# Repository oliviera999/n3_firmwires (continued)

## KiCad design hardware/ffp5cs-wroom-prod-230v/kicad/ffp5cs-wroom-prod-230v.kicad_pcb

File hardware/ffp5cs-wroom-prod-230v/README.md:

# Carte porteuse ffp5cs `wroom-prod` — VARIANTE 230 V (KiCad)

Variante **secteur** de la carte porteuse [`hardware/ffp5cs-wroom-prod/`](../ffp5cs-wroom-prod/)
(qui reste la référence 12/24 V). Même firmware, même brochage (vérifié contre
`ffp5cs/include/pins.h`), mais **6 relais** (4 métier + **2 auxiliaires AUX1/AUX2**,
GPIO 23/25, firmware ≥ v15.26) commutent des **charges 230 V ≤ 10 A** dans une
**zone secteur physiquement isolée**, et la connectique est pensée « zéro
soudure » : tout se branche en borniers à vis ou en Dupont.

```
kicad/ffp5cs-wroom-prod-230v.*   Projet KiCad 8 (schéma, PCB ROUTÉ, règles DRC .kicad_dru)
exports/gerbers-*.zip            Fabrication (Gerbers + perçages) — 234 x 110 mm, 2 couches
BOM.csv                          Nomenclature
ACHATS.md                        Liste d'achat complète (BOM + périphériques + boîtier + outillage)
generator/generate.py            Régénère schéma + PCB (non routé) + BOM depuis pinmap.json
generator/route_230v.py          Pipeline de routage sécurisé (voir ci-dessous)
tools/check_pinmap_vs_firmware.py  Garde anti-dérive code <-> plan
```

## Sécurité 230 V — comment c'est construit

- **Zone secteur dédiée** en haut de carte : seuls les contacts relais, leurs pistes
  (2,5 mm) et les borniers y vivent. Les plans de masse et le routage logique en sont
  **exclus par construction** (zones interdites pendant l'autoroutage, pours GND
  arrêtés à la frontière).
- **Fentes d'isolement fraisées** entre les 6 canaux, à la frontière droite de la
  zone, et de part et d'autre du pad COM de chaque relais (le point faible du
  boîtier SRD, où COM passe à ~3,5 mm de la bobine).
- **Règle DRC dédiée** (`.kicad_dru`) : tout cuivre de classe `Mains` doit rester à
  **≥ 3 mm** de tout cuivre non-Mains — vérifiée par `kicad-cli pcb drc` **et** par
  un contrôle géométrique indépendant dans `route_230v.py` (double ceinture).
- Routage secteur **déterministe, tracé en dur** (pas d'autorouteur dans la zone) :
  lignes droites bornier ↔ contacts, COM passant entre les broches bobine.
- Sérigraphie : « ZONE 230V — DANGER », « NC COM NO » sous chaque bornier.
- État validé : **DRC 0 violation, 0 pad non connecté, contrôle 3 mm : 0 écart**
  (KiCad 8.0.9).

### Ce qui reste À TA CHARGE côté installation (non négociable)

1. **Protection amont** : chaque circuit 230 V commuté doit être protégé par
   fusible/disjoncteur + différentiel 30 mA. Il n'y a **pas de fusible sur la carte**
   (choix : la protection appartient au tableau/à la ligne, comme sur les modules
   relais du commerce).
2. **Boîtier obligatoire**, borniers 230 V inaccessibles au doigt, presse-étoupes.
3. Charges inductives (pompe 230 V) : prévoir un **snubber RC ou une varistance côté
   charge** pour préserver les contacts.
4. Relais SRD-05 = isolation bobine/contact d'un relais grand public (type modules
   Arduino). Pour un usage durable/humide, un relais à meilleure séparation
   (ex. Hongfa HF115F) est un upgrade raisonnable — footprint à adapter.
5. Ne jamais intervenir carte sous tension (la sérigraphie te le rappelle).

## Les trois demandes spécifiques de cette variante

- **Zéro soudure à l'usage** : charges sur borniers à vis 5,08 mm ; capteurs sur JST-XH ;
  servos, OLED, I2C sur headers ; DS18B20 et LDR sur borniers ; alim sur jack **ou** bornier.
- **TOUS les GPIO libres accessibles** sur le header J17 (1×12, Dupont) :
  `3V3, GND, EN, RX0, TX0, IO5, IO14, IO17, IO32, IO35, IO36, IO39`
  (IO35/36/39 = entrées seules ; RX0/TX0 à laisser libres pendant un flash USB ;
  IO23/IO25 ne sont plus des spares : ils pilotent les relais AUX1/AUX2).
- **Distribution d'alim supplémentaire** : bornier 5 V/GND (J18), bornier 3V3/GND (J19),
  et rail header 6 points J20 (2×5V, 2×GND, 2×3V3) pour brancher des modules en Dupont.
- **3 ports I2C libres** (J14, J21, J22 — brochage GND/VCC/SCL/SDA) en plus de
  l'OLED : 3-4 modules simultanés avec les pull-ups 4,7 k (bus < ~50 cm).

## Vue Fritzing (câblage de prototype)

`fritzing/ffp5cs-wroom-prod-230v-cablage.fzz` (Fritzing ≥ 1.0, généré par
`generator/generate_fritzing.py`) : câblage breadboard périphériques ↔ DevKit
(capteurs, servos, OLED, pull-ups), plus les headers breakout GPIO (J17, 14 pts)
et rail d'alim (J20). ⚠️ Les charges **230 V n'y figurent pas** : elles se câblent
exclusivement sur les borniers NC/COM/NO de la zone secteur de la carte, jamais
en Dupont. Ouverture vérifiée dans Fritzing (« Routing completed »).

## Régénérer / rerouter / vérifier

```bash
cd hardware/ffp5cs-wroom-prod-230v
python3 generator/generate.py          # schéma + PCB placé (NON routé) + BOM
python3 generator/route_230v.py        # autoroute la logique, trace le secteur en dur,
                                       # coud les masses, corrige les reliefs, contrôle 3 mm
python3 generator/tidy_silkscreen.py   # sérigraphie : repères vs étiquettes
python3 generator/export_fab.py        # zip Gerbers prêt JLCPCB
python3 tools/check_pinmap_vs_firmware.py
kicad-cli pcb drc --severity-error kicad/ffp5cs-wroom-prod-230v.kicad_pcb -o /tmp/drc.rpt
```

⚠️ `generate.py` écrase le PCB routé — enchaîner systématiquement avec `route_230v.py`.
Le routage livré dans `kicad/` est déjà fait et validé.

## Différences avec la carte 12/24 V

| | 12/24 V (`ffp5cs-wroom-prod`) | 230 V (ce dossier) |
|---|---|---|
| Zone secteur isolée + fentes | non (inutile) | **oui** |
| Pistes contacts relais | 2,0 mm | 2,5 mm, tracées à la main |
| Règle DRC 3 mm mains↔logique | — | **oui (.kicad_dru + contrôle python)** |
| Relais | 4 (12/24 V) | **6 (230 V, dont AUX1/AUX2 pilotés serveur)** |
| GPIO libres en header | 10 broches | **12 broches (tout le restant, dont RX0/TX0/36/39)** |
| Distribution 5V/3V3/GND | — | **2 borniers + rail 6 points** |
| Ports I2C libres | 3 (J14/J18/J19) | 3 (J14/J21/J22) |
| Taille | 150×100 mm | 234×110 mm |

Empreintes : bibliothèque officielle KiCad 8.0.9 (CC-BY-SA 4.0 + exception d'usage),
vendorées dans `generator/footprints/`.

Commander la carte : voir **[../COMMANDE_JLCPCB.md](../COMMANDE_JLCPCB.md)**.

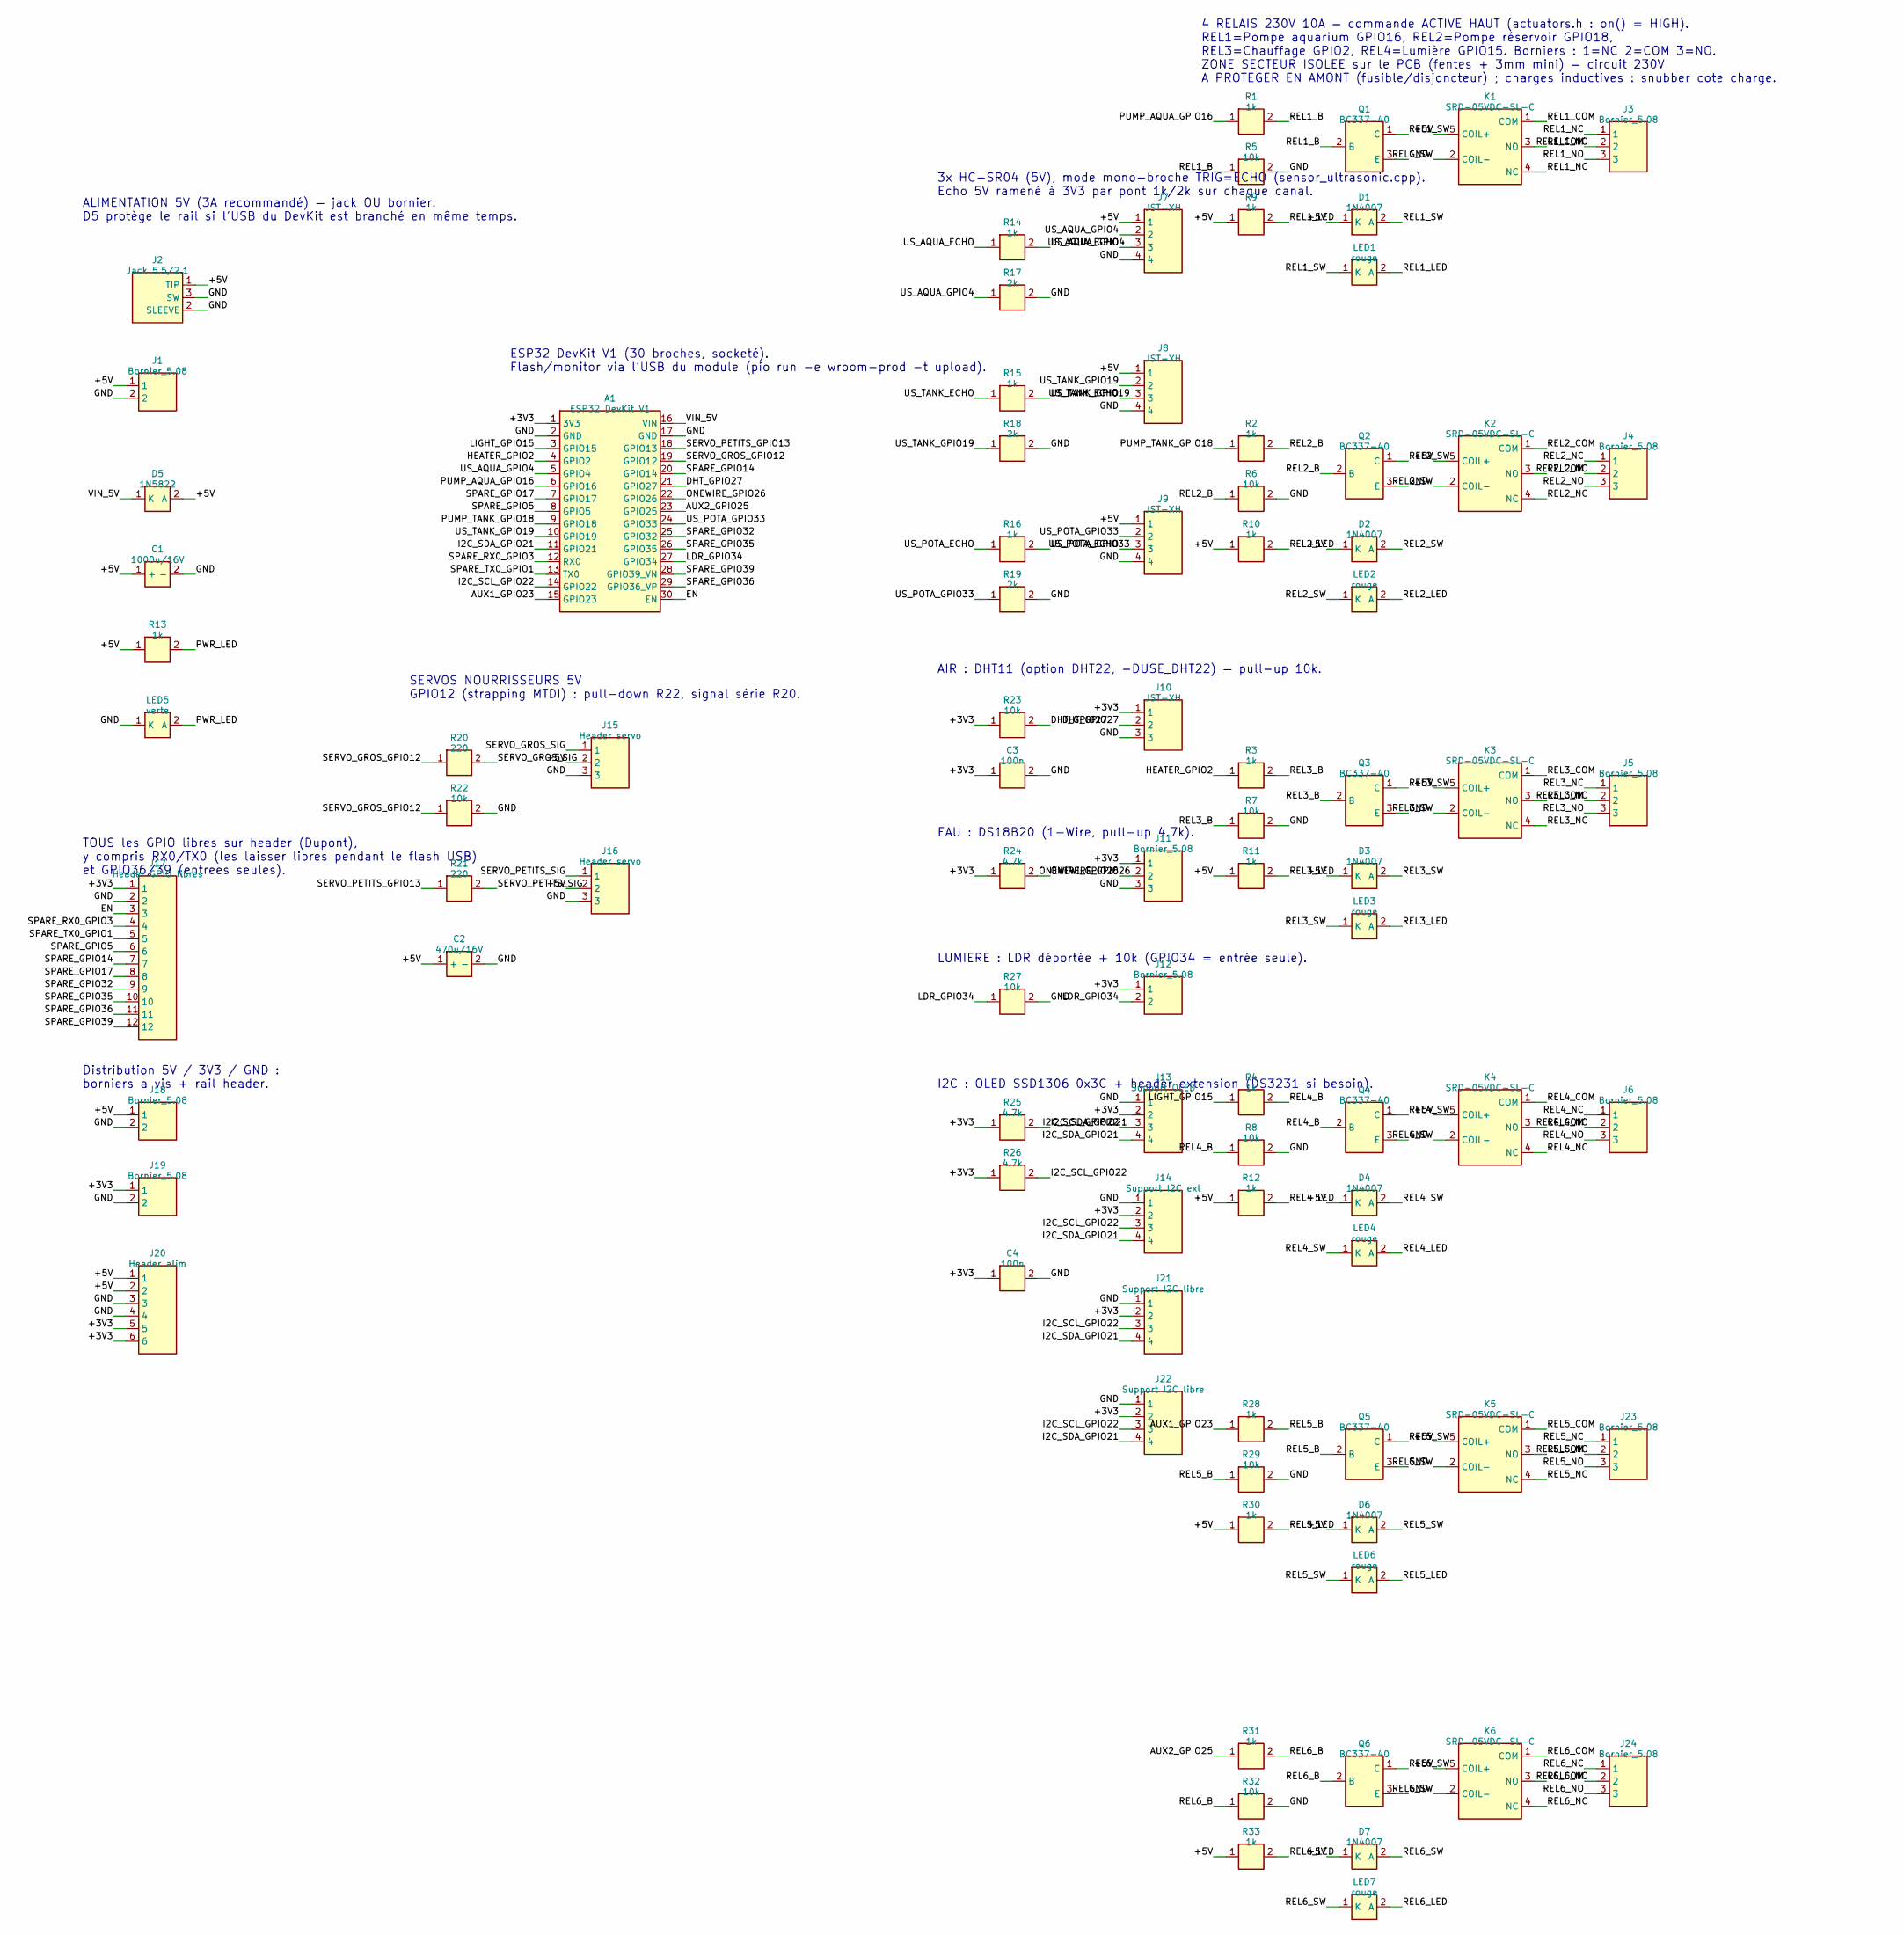
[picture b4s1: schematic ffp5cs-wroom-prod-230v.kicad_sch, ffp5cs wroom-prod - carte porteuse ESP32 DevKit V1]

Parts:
A1: ESP32 DevKit V1; ESP32_DevKit_V1_30pin
C1: 1000u/16V; CP_Radial_D10.0mm_P5.00mm
C2: 470u/16V; CP_Radial_D8.0mm_P3.50mm
C3, C4: 100n; C_Disc_D5.0mm_W2.5mm_P5.00mm
D1, D2, D3, D4, D6, D7: 1N4007; D_DO-41_SOD81_P10.16mm_Horizontal
D5: 1N5822; D_DO-201AD_P15.24mm_Horizontal
J1, J12, J18, J19: Bornier_5.08; TerminalBlock_bornier-2_P5.08mm
J2: Jack 5.5/2.1; BarrelJack_Horizontal
J3, J4, J5, J6, J11, J23, J24: Bornier_5.08; TerminalBlock_bornier-3_P5.08mm
J7, J8, J9: JST-XH; JST_XH_B4B-XH-A_1x04_P2.50mm_Vertical
J10: JST-XH; JST_XH_B3B-XH-A_1x03_P2.50mm_Vertical
J13: Support OLED; PinSocket_1x04_P2.54mm_Vertical
J14: Support I2C ext; PinSocket_1x04_P2.54mm_Vertical
J15, J16: Header servo; PinHeader_1x03_P2.54mm_Vertical
J17: Header GPIO libres; PinHeader_1x12_P2.54mm_Vertical
J20: Header alim; PinHeader_1x06_P2.54mm_Vertical
J21, J22: Support I2C libre; PinSocket_1x04_P2.54mm_Vertical
K1, K2, K3, K4, K5, K6: SRD-05VDC-SL-C; Relay_SPDT_SANYOU_SRD_Series_Form_C
LED1, LED2, LED3, LED4, LED6, LED7: rouge; LED_D5.0mm
LED5: verte; LED_D5.0mm
Q1, Q2, Q3, Q4, Q5, Q6: BC337-40; TO-92_Inline
R1, R2, R3, R4, R9, R10, R11, R12, R13, R14, R15, R16, R28, R30, R31, R33: 1k; R_Axial_DIN0207_L6.3mm_D2.5mm_P10.16mm_Horizontal
R5, R6, R7, R8, R22, R23, R27, R29, R32: 10k; R_Axial_DIN0207_L6.3mm_D2.5mm_P10.16mm_Horizontal
R17, R18, R19: 2k; R_Axial_DIN0207_L6.3mm_D2.5mm_P10.16mm_Horizontal
R20, R21: 220; R_Axial_DIN0207_L6.3mm_D2.5mm_P10.16mm_Horizontal
R24, R25, R26: 4.7k; R_Axial_DIN0207_L6.3mm_D2.5mm_P10.16mm_Horizontal

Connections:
+3V3: A1.1 (3V3), C3.1, C4.1, J10.1, J11.1, J12.1, J13.2, J14.2, J17.1, J19.1, J20.5, J20.6, J21.2, J22.2, R23.1, R24.1, R25.1, R26.1
+5V: C1.1 (+), C2.1 (+), D1.1 (K), D2.1 (K), D3.1 (K), D4.1 (K), D5.2 (A), D6.1 (K), D7.1 (K), J1.1, J2.1 (TIP), J7.1, J8.1, J9.1, J15.2, J16.2, J18.1, J20.1, J20.2, K1.5 (COIL+), K2.5 (COIL+), K3.5 (COIL+), K4.5 (COIL+), K5.5 (COIL+), K6.5 (COIL+), R9.1, R10.1, R11.1, R12.1, R13.1, R30.1, R33.1
AUX1_GPIO23: A1.15 (GPIO23), R28.1
AUX2_GPIO25: A1.23 (GPIO25), R31.1
DHT_GPIO27: A1.21 (GPIO27), J10.2, R23.2
EN: A1.30 (EN), J17.3
GND: A1.2 (GND), A1.17 (GND), C1.2 (-), C2.2 (-), C3.2, C4.2, J1.2, J2.2 (SLEEVE), J2.3 (SW), J7.4, J8.4, J9.4, J10.3, J11.3, J13.1, J14.1, J15.3, J16.3, J17.2, J18.2, J19.2, J20.3, J20.4, J21.1, J22.1, LED5.1 (K), Q1.3 (E), Q2.3 (E), Q3.3 (E), Q4.3 (E), Q5.3 (E), Q6.3 (E), R5.2, R6.2, R7.2, R8.2, R17.2, R18.2, R19.2, R22.2, R27.2, R29.2, R32.2
HEATER_GPIO2: A1.4 (GPIO2), R3.1
I2C_SCL_GPIO22: A1.14 (GPIO22), J13.3, J14.3, J21.3, J22.3, R26.2
I2C_SDA_GPIO21: A1.11 (GPIO21), J13.4, J14.4, J21.4, J22.4, R25.2
LDR_GPIO34: A1.27 (GPIO34), J12.2, R27.1
LIGHT_GPIO15: A1.3 (GPIO15), R4.1
ONEWIRE_GPIO26: A1.22 (GPIO26), J11.2, R24.2
PUMP_AQUA_GPIO16: A1.6 (GPIO16), R1.1
PUMP_TANK_GPIO18: A1.9 (GPIO18), R2.1
PWR_LED: LED5.2 (A), R13.2
REL1_B: Q1.2 (B), R1.2, R5.1
REL1_COM: J3.2, K1.1 (COM)
REL1_LED: LED1.2 (A), R9.2
REL1_NC: J3.1, K1.4 (NC)
REL1_NO: J3.3, K1.3 (NO)
REL1_SW: D1.2 (A), K1.2 (COIL-), LED1.1 (K), Q1.1 (C)
REL2_B: Q2.2 (B), R2.2, R6.1
REL2_COM: J4.2, K2.1 (COM)
REL2_LED: LED2.2 (A), R10.2
REL2_NC: J4.1, K2.4 (NC)
REL2_NO: J4.3, K2.3 (NO)
REL2_SW: D2.2 (A), K2.2 (COIL-), LED2.1 (K), Q2.1 (C)
REL3_B: Q3.2 (B), R3.2, R7.1
REL3_COM: J5.2, K3.1 (COM)
REL3_LED: LED3.2 (A), R11.2
REL3_NC: J5.1, K3.4 (NC)
REL3_NO: J5.3, K3.3 (NO)
REL3_SW: D3.2 (A), K3.2 (COIL-), LED3.1 (K), Q3.1 (C)
REL4_B: Q4.2 (B), R4.2, R8.1
REL4_COM: J6.2, K4.1 (COM)
REL4_LED: LED4.2 (A), R12.2
REL4_NC: J6.1, K4.4 (NC)
REL4_NO: J6.3, K4.3 (NO)
REL4_SW: D4.2 (A), K4.2 (COIL-), LED4.1 (K), Q4.1 (C)
REL5_B: Q5.2 (B), R28.2, R29.1
REL5_COM: J23.2, K5.1 (COM)
REL5_LED: LED6.2 (A), R30.2
REL5_NC: J23.1, K5.4 (NC)
REL5_NO: J23.3, K5.3 (NO)
REL5_SW: D6.2 (A), K5.2 (COIL-), LED6.1 (K), Q5.1 (C)
REL6_B: Q6.2 (B), R31.2, R32.1
REL6_COM: J24.2, K6.1 (COM)
REL6_LED: LED7.2 (A), R33.2
REL6_NC: J24.1, K6.4 (NC)
REL6_NO: J24.3, K6.3 (NO)
REL6_SW: D7.2 (A), K6.2 (COIL-), LED7.1 (K), Q6.1 (C)
SERVO_GROS_GPIO12: A1.19 (GPIO12), R20.1, R22.1
SERVO_GROS_SIG: J15.1, R20.2
SERVO_PETITS_GPIO13: A1.18 (GPIO13), R21.1
SERVO_PETITS_SIG: J16.1, R21.2
SPARE_GPIO5: A1.8 (GPIO5), J17.6
SPARE_GPIO14: A1.20 (GPIO14), J17.7
SPARE_GPIO17: A1.7 (GPIO17), J17.8
SPARE_GPIO32: A1.25 (GPIO32), J17.9
SPARE_GPIO35: A1.26 (GPIO35), J17.10
SPARE_GPIO36: A1.29 (GPIO36_VP), J17.11
SPARE_GPIO39: A1.28 (GPIO39_VN), J17.12
SPARE_RX0_GPIO3: A1.12 (RX0), J17.4
SPARE_TX0_GPIO1: A1.13 (TX0), J17.5
US_AQUA_ECHO: J7.3, R14.1
US_AQUA_GPIO4: A1.5 (GPIO4), J7.2, R14.2, R17.1
US_POTA_ECHO: J9.3, R16.1
US_POTA_GPIO33: A1.24 (GPIO33), J9.2, R16.2, R19.1
US_TANK_ECHO: J8.3, R15.1
US_TANK_GPIO19: A1.10 (GPIO19), J8.2, R15.2, R18.1
VIN_5V: A1.16 (VIN), D5.1 (K)

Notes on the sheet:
ALIMENTATION 5V (3A recommandé) — jack OU bornier. D5 protège le rail si l'USB du DevKit est branché en même temps.
ESP32 DevKit V1 (30 broches, socketé). Flash/monitor via l'USB du module (pio run -e wroom-prod -t upload).
SERVOS NOURRISSEURS 5V GPIO12 (strapping MTDI) : pull-down R22, signal série R20.
3x HC-SR04 (5V), mode mono-broche TRIG=ECHO (sensor_ultrasonic.cpp). Echo 5V ramené à 3V3 par pont 1k/2k sur chaque canal.
AIR : DHT11 (option DHT22, -DUSE_DHT22) — pull-up 10k.
EAU : DS18B20 (1-Wire, pull-up 4.7k).
LUMIERE : LDR déportée + 10k (GPIO34 = entrée seule).
I2C : OLED SSD1306 0x3C + header extension (DS3231 si besoin).
4 RELAIS 230V 10A — commande ACTIVE HAUT (actuators.h : on() = HIGH). REL1=Pompe aquarium GPIO16, REL2=Pompe réservoir GPIO18, REL3=Chauffage GPIO2, REL4=Lumière GPIO15. Borniers : 1=NC 2=COM 3=NO. ZONE SECTEUR ISOLEE sur le PCB (fentes + 3mm mini) — circuit 230V A PROTEGER EN AMONT (fusible/disjon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
TOUS les GPIO libres sur header (Dupont), y compris RX0/TX0 (les laisser libres pendant le flash USB) et GPIO36/39 (entrees seules).
Distribution 5V / 3V3 / GND : borniers a vis + rail header.

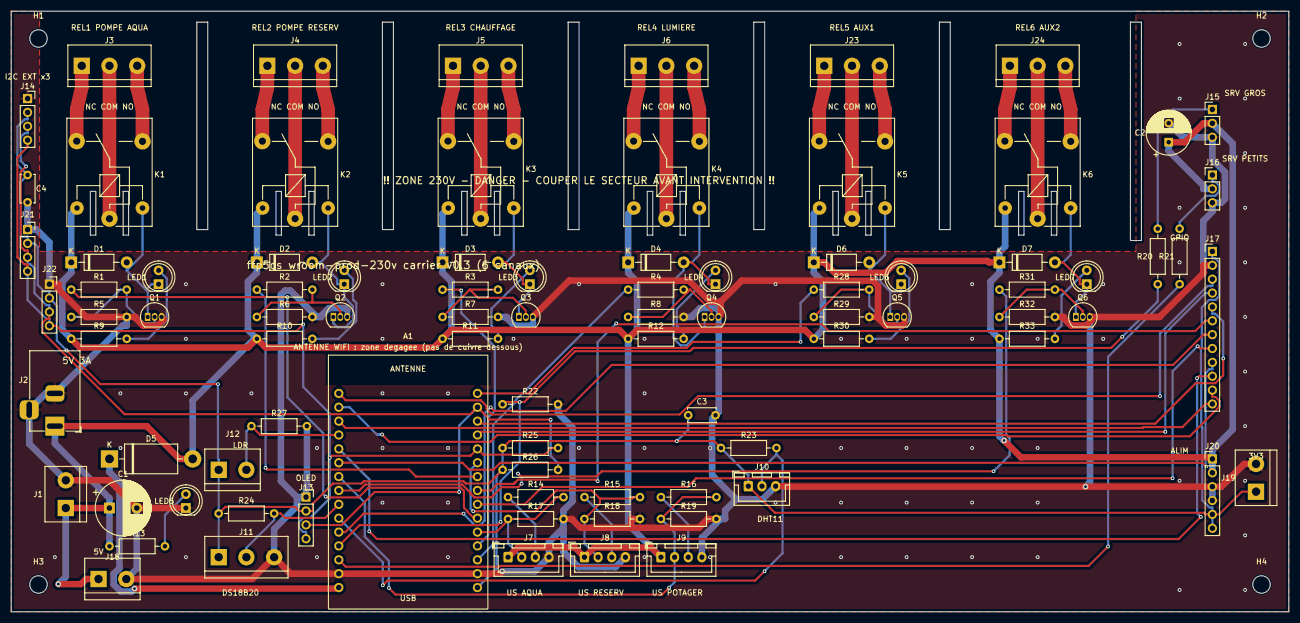
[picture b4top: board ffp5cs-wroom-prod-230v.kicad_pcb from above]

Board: 2 copper layers, 234.0 x 110.0 mm, 92 parts (0 on the bottom side), 72 nets.

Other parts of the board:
H1, H2, H3, H4: M3; MountingHole_3.2mm_M3

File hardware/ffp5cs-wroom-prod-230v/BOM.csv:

Refs;Qte;Valeur;Empreinte;Description
A1;1;ESP32 DevKit V1;ESP32_DevKit_V1_30pin;Module ESP32-WROOM-32 DevKit V1 30 broches, sur 2 supports 1x15
C1;1;1000u/16V;CP_Radial_D10.0mm_P5.00mm;Réservoir rail 5V (relais + servos + HC-SR04)
C2;1;470u/16V;CP_Radial_D8.0mm_P3.50mm;Découplage rail 5V servos
C3;1;100n;C_Disc_D5.0mm_W2.5mm_P5.00mm;Découplage 3V3 capteurs
C4;1;100n;C_Disc_D5.0mm_W2.5mm_P5.00mm;Découplage 3V3 I2C
D1 D2 D3 D4 D6 D7;6;1N4007;D_DO-41_SOD81_P10.16mm_Horizontal;Diode de roue libre bobine
D5;1;1N5822;D_DO-201AD_P15.24mm_Horizontal;Schottky 3A vers VIN DevKit (anti-retour si USB branché)
H1 H2 H3 H4;4;M3;MountingHole_3.2mm_M3;Trou de fixation M3
J1;1;Bornier_5.08;TerminalBlock_bornier-2_P5.08mm;Entrée 5V alternative (bornier, 1=+5V 2=GND)
J10;1;JST-XH;JST_XH_B3B-XH-A_1x03_P2.50mm_Vertical;DHT11/DHT22 (1=3V3 2=DATA 3=GND)
J11;1;Bornier_5.08;TerminalBlock_bornier-3_P5.08mm;Sonde DS18B20 étanche (1=3V3 2=DATA 3=GND)
J12;1;Bornier_5.08;TerminalBlock_bornier-2_P5.08mm;LDR déportée entre 3V3 et l'ADC (1=3V3 2=ADC)
J13;1;Support OLED;PinSocket_1x04_P2.54mm_Vertical;OLED SSD1306 128x64 I2C 0x3C (1=GND 2=VCC 3=SCL 4=SDA)
J14;1;Support I2C ext;PinSocket_1x04_P2.54mm_Vertical;Extension I2C — ex. module DS3231 (1=GND 2=VCC 3=SCL 4=SDA)
J15;1;Header servo;PinHeader_1x03_P2.54mm_Vertical;Servo GROS (1=SIG 2=+5V 3=GND)
J16;1;Header servo;PinHeader_1x03_P2.54mm_Vertical;Servo PETITS (1=SIG 2=+5V 3=GND)
J17;1;Header GPIO libres;PinHeader_1x12_P2.54mm_Vertical;TOUS les GPIO libres (1=3V3 2=GND 3=EN 4=RX0 5=TX0 6=IO5 7=IO14 8=IO17 9=IO32 10=IO35 11=IO36 12=IO39) — IO23/IO25 = relais AUX
J18;1;Bornier_5.08;TerminalBlock_bornier-2_P5.08mm;Distribution 5V (1=+5V 2=GND)
J19;1;Bornier_5.08;TerminalBlock_bornier-2_P5.08mm;Distribution 3V3 (1=+3V3 2=GND)
J2;1;Jack 5.5/2.1;BarrelJack_Horizontal;Entrée 5V 3A (jack, centre = +)
J20;1;Header alim;PinHeader_1x06_P2.54mm_Vertical;Rail Dupont (1-2=+5V 3-4=GND 5-6=+3V3)
J21;1;Support I2C libre;PinSocket_1x04_P2.54mm_Vertical;Port I2C libre 2 (1=GND 2=VCC 3=SCL 4=SDA)
J22;1;Support I2C libre;PinSocket_1x04_P2.54mm_Vertical;Port I2C libre 3 (1=GND 2=VCC 3=SCL 4=SDA)
J23 J24 J3 J4 J5 J6;6;Bornier_5.08;TerminalBlock_bornier-3_P5.08mm;Bornier charge 230V (1=NC 2=COM 3=NO)
J7;1;JST-XH;JST_XH_B4B-XH-A_1x04_P2.50mm_Vertical;HC-SR04 AQUA (1=5V 2=TRIG 3=ECHO 4=GND)
J8;1;JST-XH;JST_XH_B4B-XH-A_1x04_P2.50mm_Vertical;HC-SR04 TANK (1=5V 2=TRIG 3=ECHO 4=GND)
J9;1;JST-XH;JST_XH_B4B-XH-A_1x04_P2.50mm_Vertical;HC-SR04 POTA (1=5V 2=TRIG 3=ECHO 4=GND)
K1 K2 K3 K4 K5 K6;6;SRD-05VDC-SL-C;Relay_SPDT_SANYOU_SRD_Series_Form_C;Relais 5V SPDT 10A/250VAC (Songle/Sanyou SRD)
LED1 LED2 LED3 LED4 LED6 LED7;6;rouge;LED_D5.0mm;LED témoin relais ON
LED5;1;verte;LED_D5.0mm;LED présence 5V
Q1 Q2 Q3 Q4 Q5 Q6;6;BC337-40;TO-92_Inline;Transistor NPN commande relais (1=C 2=B 3=E)
R1 R2 R28 R3 R31 R4;6;1k;R_Axial_DIN0207_L6.3mm_D2.5mm_P10.16mm_Horizontal;Résistance base transistor
R13;1;1k;R_Axial_DIN0207_L6.3mm_D2.5mm_P10.16mm_Horizontal;Résistance LED présence 5V
R14;1;1k;R_Axial_DIN0207_L6.3mm_D2.5mm_P10.16mm_Horizontal;Série écho HC-SR04 AQUA
R15;1;1k;R_Axial_DIN0207_L6.3mm_D2.5mm_P10.16mm_Horizontal;Série écho HC-SR04 TANK
R16;1;1k;R_Axial_DIN0207_L6.3mm_D2.5mm_P10.16mm_Horizontal;Série écho HC-SR04 POTA
R17;1;2k;R_Axial_DIN0207_L6.3mm_D2.5mm_P10.16mm_Horizontal;Pont diviseur écho AQUA (5V->3V3)
R18;1;2k;R_Axial_DIN0207_L6.3mm_D2.5mm_P10.16mm_Horizontal;Pont diviseur écho TANK (5V->3V3)
R19;1;2k;R_Axial_DIN0207_L6.3mm_D2.5mm_P10.16mm_Horizontal;Pont diviseur écho POTA (5V->3V3)
R20;1;220;R_Axial_DIN0207_L6.3mm_D2.5mm_P10.16mm_Horizontal;Série signal servo gros
R21;1;220;R_Axial_DIN0207_L6.3mm_D2.5mm_P10.16mm_Horizontal;Série signal servo petits
R22;1;10k;R_Axial_DIN0207_L6.3mm_D2.5mm_P10.16mm_Horizontal;Pull-down GPIO12 (strapping MTDI : doit être bas au boot)
R23;1;10k;R_Axial_DIN0207_L6.3mm_D2.5mm_P10.16mm_Horizontal;Pull-up data DHT11
R24;1;4.7k;R_Axial_DIN0207_L6.3mm_D2.5mm_P10.16mm_Horizontal;Pull-up bus 1-Wire DS18B20
R25;1;4.7k;R_Axial_DIN0207_L6.3mm_D2.5mm_P10.16mm_Horizontal;Pull-up I2C SDA
R26;1;4.7k;R_Axial_DIN0207_L6.3mm_D2.5mm_P10.16mm_Horizontal;Pull-up I2C SCL
R27;1;10k;R_Axial_DIN0207_L6.3mm_D2.5mm_P10.16mm_Horizontal;Bas du pont diviseur LDR (GPIO34 = entrée seule ADC)
R29 R32 R5 R6 R7 R8;6;10k;R_Axial_DIN0207_L6.3mm_D2.5mm_P10.16mm_Horizontal;Pull-down base (état sûr au boot)
R10 R11 R12 R30 R33 R9;6;1k;R_Axial_DIN0207_L6.3mm_D2.5mm_P10.16mm_Horizontal;Résistance LED témoin
A1 (supports);2;Support femelle 1x15 P2.54;monte sur l'empreinte ESP32_DevKit_V1_30pin;Barrettes femelles 15 pts : le DevKit s'enfiche, jamais soudé

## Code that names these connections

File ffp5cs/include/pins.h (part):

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constexpr int ONE_WIRE_BUS = 41;  // Bus DS18B20 (37 = conflit PSRAM octale)

// I2C (Wire)
constexpr int I2C_SDA = 8;
constexpr int I2C_SCL = 9;

// OLED Display (I2C)
constexpr int OLED_SDA = I2C_SDA;
constexpr int OLED_SCL = I2C_SCL;
constexpr int OLED_ADDR = 0x3C;

// RTC DS3231 (I2C) - optionnel, pour heure précise offline
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
// SD carte (SPI) - optionnel ; broches NON câblées sur la carte porteuse
// (conservées pour compiler le support SD, à câbler via J20 le cas échéant)
constexpr int SD_CS_PIN   = 10;
constexpr int SD_MOSI_PIN = 11;
constexpr int SD_CLK_PIN  = 12;
constexpr int SD_MISO_PIN = 14;

} // namespace Pins

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// Source de vérité : pinmap_universel_propose.json. SD native (10/12/13/14),
// K5/K6 (=AUX1/AUX2) embarqués : GPIO 48 (LED RGB v1.0 : recopie d'état K5,
// cosmétique) et 45 (strapping VDD_SPI : commande via base 1k + pull-down 10k,
// sûre au boot, comme GPIO2/15 sur les cartes historiques).
namespace Pins {
constexpr int ULTRASON_AQUA = 39;  // net US1
constexpr int ULTRASON_TANK = 40;  // net US2
constexpr int ULTRASON_POTA = 41;  // net US3

constexpr int EAU_POTAGER = ULTRASON_POTA; // Alias pour rétrocompatibilité
constexpr int LUMINOSITE = 6;      // net ADC_E (ADC1_CH5)

constexpr int POMPE_AQUA   = 15;   // net K1
constexpr int POMPE_RESERV = 16;   // net K2
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constexpr int AUX1 = 48;           // net AUX1 (K5)
constexpr int AUX2 = 45;           // net AUX2 (K6)

constexpr int SERVO_GROS   = 21;   // net SERVO1
constexpr int SERVO_PETITS = 47;   // net SERVO2

constexpr int DHT_PIN      = 38;   // net DHT_INT (LED RGB v1.1 : scintillement cosmétique)
constexpr int ONE_WIRE_BUS = 42;   // net ONEWIRE

constexpr int I2C_SDA = 8;
constexpr int I2C_SCL = 9;
constexpr int OLED_SDA = I2C_SDA;
constexpr int OLED_SCL = I2C_SCL;
constexpr int OLED_ADDR = 0x3C;
constexpr uint8_t DS3231_I2C_ADDR = 0x68;

// microSD embarquée (slot bi-site de la carte, côté A2)
constexpr int SD_CS_PIN   = 10;
constexpr int SD_MOSI_PIN = 12;
constexpr int SD_CLK_PIN  = 13;
constexpr int SD_MISO_PIN = 14;

} // namespace Pins

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namespace Pins {
constexpr int ULTRASON_AQUA = 4;   // net US1 (partagé PLUIE msp)
constexpr int ULTRASON_TANK = 5;   // net US2 (partagé DHT_EXT msp)
constexpr int ULTRASON_POTA = 14;  // net US3 (= SD_CS en env wroom-sd)

constexpr int EAU_POTAGER = ULTRASON_POTA;
constexpr int LUMINOSITE = 36;     // net ADC_E (entrée seule, ADC1)

constexpr int POMPE_AQUA   = 16;   // net K1 (partagé POMPE n3pp)
constexpr int POMPE_RESERV = 17;   // net K2
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constexpr int AUX1 = 23;           // net AUX1 (K5)
constexpr int AUX2 = 25;           // net AUX2 (K6)

constexpr int SERVO_GROS   = 26;   // net SERVO1 (partagé SERVOGD msp)
constexpr int SERVO_PETITS = 27;   // net SERVO2 (partagé SERVOHB msp)

constexpr int DHT_PIN      = 15;   // net DHT_INT (commun aux 3 firmwares)
constexpr int ONE_WIRE_BUS = 2;    // net ONEWIRE (partagé TempEau msp)

constexpr int I2C_SDA = 21;
constexpr int I2C_SCL = 22;
constexpr int OLED_SDA = I2C_SDA;
constexpr int OLED_SCL = I2C_SCL;
constexpr int OLED_ADDR = 0x3C;
constexpr uint8_t DS3231_I2C_ADDR = 0x68;

// microSD (option env wroom-sd uniquement — lignes sur US3/AUX1/AUX2 + 12)
constexpr int SD_CS_PIN   = 14;
constexpr int SD_CLK_PIN  = 23;
constexpr int SD_MOSI_PIN = 25;
constexpr int SD_MISO_PIN = 12;    // strapping MTDI : ligne SANS pull-up sur la carte

} // namespace Pins

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constexpr int ONE_WIRE_BUS = 37;  // Bus DS18B20

// I2C (Wire) - Pins par défaut pour ESP32-S3 devkit. Vérifier câblage (VCC/GND/SDA/SCL) et pull-ups si OLED erratique (voir i2c_bus.cpp).
constexpr int I2C_SDA = 8;  // GPIO 8 (SDA)
constexpr int I2C_SCL = 9;  // GPIO 9 (SCL)

// OLED Display (I2C)
constexpr int OLED_SDA = I2C_SDA;
constexpr int OLED_SCL = I2C_SCL;
constexpr int OLED_ADDR = 0x3C;  // Adresse I2C de l'OLED

// RTC DS3231 (I2C) - optionnel, pour heure précise offline
constexpr uint8_t DS3231_I2C_ADDR = 0x68;

// SD carte (SPI) - optionnel, broches 10/11/12/14 (libres, non utilisées par les servos)
constexpr int SD_CS_PIN   = 10;
constexpr int SD_MOSI_PIN = 11;
constexpr int SD_CLK_PIN  = 12;
constexpr int SD_MISO_PIN = 14;

} // namespace Pins

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constexpr int ONE_WIRE_BUS = 26;

// I2C (Wire) - Pins par défaut pour ESP32. Vérifier câblage (VCC/GND/SDA/SCL) et pull-ups si OLED erratique (voir i2c_bus.cpp).
constexpr int I2C_SDA = 21;  // GPIO 21 (SDA)
constexpr int I2C_SCL = 22;  // GPIO 22 (SCL)

// OLED Display (I2C)
constexpr int OLED_SDA = I2C_SDA;
constexpr int OLED_SCL = I2C_SCL;
constexpr int OLED_ADDR = 0x3C;  // Adresse I2C de l'OLED

// RTC DS3231 (I2C) - optionnel, pour heure précise offline
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
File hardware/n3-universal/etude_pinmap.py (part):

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    "US2":      {"ffp5cs": "ULTRASON_TANK", "msp": "DHT_EXT (legacy, préférer BME280 0x77)"},
    "US3":      {"ffp5cs": "ULTRASON_POTA"},
    # capteurs partout
    "DHT_INT":  {"msp": "DHTPININT", "n3pp": "DHT", "ffp5cs": "DHT_PIN"},
    "ONEWIRE":  {"msp": "TempEau (DS18B20)", "ffp5cs": "DS18B20"},
    # power-gate (rail +3V3_SW) — bypass fermé par défaut (jumper) pour ffp5cs
    "GATE":     {"msp": "RELAIS (gate)", "n3pp": "RELAIS (gate)"},
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# ESP32-S3-DevKitC-1 44p — politique STRICTE puis PRAGMATIQUE
S3_ALL = {1, 2, 3, 4, 5, 6, 7, 8, 9, 10, 11, 12, 13, 14, 15, 16, 17, 18, 21,
          38, 39, 40, 41, 42, 45, 47, 48}
S3_ADC1 = set(range(1, 11))            # ADC1 = GPIO1..10 (ADC2 inutilisable WiFi)
S3_STRICT_EXCLUDE = {3, 45, 38, 48, 11}    # strapping (3/45), LED RGB (38/48), 11 = réserve non câblée
S3_PRAGMATIC_CAVEATS = {
    3:  "strapping JTAG-sel (sans effet hors eFuse JTAG) ; pas de pull-up sur la broche (R34 1k → base Q8)",
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# Variante « WROOM + SD universelle » : le slot microSD (unique, câblé en dur)
# monte sur des nets que msp et n3pp N'UTILISENT PAS — ils gardent donc TOUTES
# leurs fonctions, SD comprise, sans arbitrage :
#   SD_CS   = GPIO14 (net US3 — ultrason potager, ffp5cs seulement)
#   SD_CLK  = GPIO23 (net AUX1 — breakout, ffp5cs seulement)
#   SD_MOSI = GPIO25 (net AUX2 — breakout, ffp5cs seulement)
#   SD_MISO = GPIO12 (broche libre ; strapping MTDI : AUCUN pull-up, socket nu)
# Seul ffp5cs-sur-WROOM doit choisir, PAR ENV DE BUILD (mécanisme PINMAP_* déjà
# en place) : env « wroom-sd » = SD active, renonce à US_POTA + AUX1/AUX2 ;
# env standard = 3 ultrasons + AUX, pas de SD. ffp5cs-sur-S3 n'arbitre rien
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NETS_WROOM_SD["AUX2"].update({"msp": "SD_MOSI (option SD)", "n3pp": "SD_MOSI (option SD)"})
NETS_WROOM_SD["AUX2"]["ffp5cs"] = "AUX2 — ou SD_MOSI en env wroom-sd"
NETS_WROOM_SD["SD_MISO"] = {"msp": "SD_MISO", "n3pp": "SD_MISO",
                            "ffp5cs": "SD_MISO (GPIO12 : AUCUN pull-up, socket nu)"}
WROOM_SD_OPTION = {"SD_MISO": 12}

WROOM_MAP = {
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    "SERVO1": 26, "SERVO2": 27,
    "US1": 4, "US2": 5, "US3": 14,
    "DHT_INT": 15, "ONEWIRE": 2, "GATE": 13,
    # SD : absente du site WROOM (S3 uniquement) ; GPIO12 reste libre (header)
}
S3_MAP = {
    "I2C_SDA": 8, "I2C_SCL": 9,
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    "SERVO1": 21, "SERVO2": 47,
    "US1": 39, "US2": 40, "US3": 41,
    "ONEWIRE": 42,
    "GATE": 3,          # JTAG inutilisé ; R35 tire la grille de Q7 → rail +3V3_SW OFF au boot tant que GPIO3 n'est pas HAUT (ou JP1 fermé)
    "DHT_INT": 38,      # caveat LED v1.1 (cosmétique)
    "AUX1": 48,         # caveat LED v1.0 (cosmétique, breakout)
    "AUX2": 45,         # caveat strapping : entrée de module relais SANS pull-up
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
## Addendum audit final rev 0.1 (2026-08-27)

- **GPIO12/MTDI + module microSD (WROOM)** : la précaution « socket nu, aucun
  pull-up » ne couvre pas un module ENFICHÉ avec carte : le pull-up interne DAT0
  de la carte SD (et a fortiori un module tamponné type Catalex) peut tirer MTDI
  haut à l'échantillonnage du strap → VDD_SDIO 1,8 V, boot en échec. Consigne :
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
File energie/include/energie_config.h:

#pragma once
/**
 * Banc d'essai energie — configuration (ESP32-S3 + 3 x INA226).
 *
 * Voies : panneau solaire (production), batterie plomb/AGM 12 V (charge /
 * decharge), consommation des peripheriques. Shunt, courant max, sens et gain
 * sont reglables ici ET a chaud par la console serie (persistes en NVS).
 *
 * Secrets : credentials.h a la racine du depot (meme fichier que n3pp/msp) :
 * WIFI_SSIDx/WIFI_PASSx, API_KEY, API_SIG_SECRET, SMTP_*.
 */

#include "credentials.h"
#include "n3_defaults.h"

#ifndef API_SIG_SECRET
#define API_SIG_SECRET ""
#endif

// -----------------------------------------------------------------------------
// Version (source unique — cf. firmwares.manifest.json, versionSource)
// -----------------------------------------------------------------------------
#define FIRMWARE_VERSION "0.2"
#define ENERGIE_SENSOR_NAME "energie"

// -----------------------------------------------------------------------------
// Broches (ESP32-S3-DevKitC-1 N16R8 ; carte n3-universal, PINMAP_UNIVERSAL)
// GPIO33-37 interdits (PSRAM octale). Ne jamais utiliser LED_BUILTIN /
// neopixelWrite : GPIO48 = relais K5 sur n3-universal.
// -----------------------------------------------------------------------------
#define ENERGIE_PIN_SDA 8
#define ENERGIE_PIN_SCL 9
#define ENERGIE_I2C_HZ 100000UL  // 100 kHz : OLED + DS3231 + 3 INA, cables courts

// GATE du rail +3V3_SW (n3-universal, Q8 via R34) : coupe au boot si JP1 != 1-2.
// Mis a HAUT au demarrage pour alimenter les prises I2C (OLED/INA). -1 = inutilise.
#define ENERGIE_PIN_RAIL_GATE 3
#define ENERGIE_RAIL_SETTLE_MS 100

// Relais n3-universal (drivers actifs HAUT, pull-down 10 k) : forces a BAS
// (OFF) au boot pour qu'un banc monte sur la carte ne commute rien.
// K1..K4 = 15..18, K5 = 48 (= LED RGB du DevKit), K6 = 45.
#define ENERGIE_SAFE_LOW_PINS {15, 16, 17, 18, 48, 45}

// Broche ALERT des INA (non routee sur les PCB : polling 1 Hz). -1 = inutilisee.
#define ENERGIE_PIN_INA_ALERT -1

// Pont diviseur batterie de la carte n3-universal (ADC_VBAT = GPIO7, 100k/22k :
// pleine echelle ~17 V, au-dessus de l'absorption AGM 14,4-14,7 V ; l'ancien 27k
// saturait vers 14,6 V), lu en option pour comparaison avec l'INA batterie.
// -1 = desactive (DevKit nu).
#define ENERGIE_PIN_ADC_VBAT -1
#define ENERGIE_VBAT_R1 100000UL
#define ENERGIE_VBAT_R2 22000UL
#define ENERGIE_VBAT_VREF 3.3f

// -----------------------------------------------------------------------------
// Voies INA226 (adresses prevues par la doc n3-universal : 0x40 / 0x41 / 0x44)
// Shunt par defaut = module standard « R100 » (0,1 ohm) -> 0,82 A max !
// Module reel (panneau 50-80 Wc, batterie, conso) : shunt externe 5-10 mohm.
// -----------------------------------------------------------------------------
#define ENERGIE_CH_COUNT 3
#define ENERGIE_CH_PANNEAU 0
#define ENERGIE_CH_BATTERIE 1
#define ENERGIE_CH_CONSO 2

#define ENERGIE_PANNEAU_ADDR 0x40
#define ENERGIE_PANNEAU_SHUNT_OHM 0.1f
#define ENERGIE_PANNEAU_IMAX_A 0.8f
#define ENERGIE_PANNEAU_INVERT false

#define ENERGIE_BATTERIE_ADDR 0x41
#define ENERGIE_BATTERIE_SHUNT_OHM 0.1f
#define ENERGIE_BATTERIE_IMAX_A 0.8f
// Convention : courant batterie > 0 = CHARGE. Mettre true si le module est
// cable a l'envers (verifier avec la commande « dump » en charge).
#define ENERGIE_BATTERIE_INVERT false

#define ENERGIE_CONSO_ADDR 0x44
#define ENERGIE_CONSO_SHUNT_OHM 0.1f
#define ENERGIE_CONSO_IMAX_A 0.8f
#define ENERGIE_CONSO_INVERT false

// Moyennage materiel : 128 x (1,1 ms bus + 1,1 ms shunt) ~ 282 ms par resultat,
// lisse le hachage d'un regulateur PWM. Reglable par la commande « avg ».
#define ENERGIE_INA_AVG_SAMPLES 128
#define ENERGIE_INA_CONV_US 1100

// -----------------------------------------------------------------------------
// Cadences
// -----------------------------------------------------------------------------
#define ENERGIE_SAMPLE_MS 1000UL          // mesure (1 Hz)
#define ENERGIE_POST_MS 10000UL           // envoi serveur (moyennes + energie de la fenetre)
#define ENERGIE_MAX_GAP_MS 30000UL        // trou de mesure au-dela duquel on n'integre pas
#define ENERGIE_DISPLAY_MS 1000UL
#define ENERGIE_WIFI_RETRY_MS 30000UL     // nouvelle session WiFi apres echec
#define ENERGIE_SOC_SAVE_MS 900000UL      // sauvegarde NVS du SoC (15 min)

// -----------------------------------------------------------------------------
// Batterie plomb/AGM 12 V
// -----------------------------------------------------------------------------
#define ENERGIE_BAT_CAPACITY_AH 12.0f
#define ENERGIE_BAT_CHARGE_EFFICIENCY 0.90f
#define ENERGIE_BAT_REST_CURRENT_A 0.12f   // ~C/100
#define ENERGIE_BAT_REST_SECONDS 1800UL    // repos avant recalage OCV

// Alerte mail batterie basse (n3_mail, SMTP de credentials.h)
#define ENERGIE_ALERT_ENABLED 1
#define ENERGIE_ALERT_LOW_V 11.8f
#define ENERGIE_ALERT_HOLD_S 60UL
#define ENERGIE_ALERT_REARM_V 12.4f
#define ENERGIE_ALERT_COOLDOWN_S 21600UL   // 6 h
#define ENERGIE_ALERT_CHARGING_A 0.05f

// -----------------------------------------------------------------------------
// Serveur (famille « energie » de n3_serveur)
// -----------------------------------------------------------------------------
#ifdef USE_HTTPS_ENDPOINTS
#define ENERGIE_SERVER_SCHEME "https://"
#else
#define ENERGIE_SERVER_SCHEME "http://"
#endif

#ifdef TEST_MODE
#define ENERGIE_POST_URL ENERGIE_SERVER_SCHEME "iot.olution.info/energie-test/post-data"
#else
#define ENERGIE_POST_URL ENERGIE_SERVER_SCHEME "iot.olution.info/energie/post-data"
#endif

#define ENERGIE_OTA_TITLE "ENERGIE OTA"
#define ENERGIE_OTA_URL_PROD "http://iot.olution.info/ota/energie/metadata.json"
#define ENERGIE_OTA_URL_TEST "http://iot.olution.info/ota/energie-test/metadata.json"

// -----------------------------------------------------------------------------
// OLED SSD1306 (prise J13 n3-universal)
// -----------------------------------------------------------------------------
#define ENERGIE_OLED_ADDR 0x3C

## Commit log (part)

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2026-06-09 refactor(ffp5cs): extrait postSenderTask d'app_tasks (app_tasks_post.cpp)
    postSenderTask (envoi fire-and-forget POST/heartbeat) -> app_tasks_post.cpp.
    PostSenderType/PostSenderMsg déplacés dans app_tasks_internal.h (partagés
    producteur netTask / consommateur postSenderTask) ; g_postSenderQueue passé
    en linkage externe. app_tasks.cpp : 1163 -> 1098 lignes.
    Cumul refonte (pool+web+sensor+mail+ota+post) : 1788 -> 1098 (-39%).
    Build wroom-test OK.
2026-06-09 fix(build): vrai build Linux/CI (pio_repair_build_junction sys.exit) + erreurs de compilation exposées
    CRITIQUE : scripts/pio_repair_build_junction.py faisait sys.exit(0) sur les
    plateformes sans redirection (Linux/CI), terminant 'pio run' AVANT la
    compilation -> le build 'reussissait' sans rien compiler. Donc la CI ffp5cs
    (et les builds locaux) etaient vacants : mes refactors n'avaient jamais ete
    compiles. Corrige avec le meme motif 'if root:' que pio_redirect_build_dir.py
    (Windows inchange, Linux/CI compile vraiment).
2026-06-09 ci(ffp5cs): budget flash wroom-prod 98% (partition fs_mail ~96%)
2026-06-09 docs(ffp5cs): chiffres flash réels + seuil prod 85% (DRAM = vraie contrainte)
    Build prod réel (mesuré) : flash 78,7% (partition fs_mail), pas ~96% comme
    estimé. La vraie tension de wroom-prod est la DRAM interne (~99,9%, ~108 o
    libres), gérée par le linker — pas le flash. Seuil flash prod 98% -> 85%
    (marge anti-régression réaliste). Investigation nm : décomposition neutre
    en .bss (pas de duplication), donc non responsable de la marge DRAM.
2026-06-09 refactor(ffp5cs): extrait la logique refill d'automatism.cpp (1519 -> 1224)
    8 méthodes handleRefill* (sécurités trop-plein/niveau-bas, démarrage/arrêt
    auto, durée max, récupération) -> automatism/automatism_refill.cpp (suit le
    pattern src/automatism/ existant ; méthodes membres, comportement identique,
    self-contained : aucun global de fichier). WIP : validation build en cours.
2026-06-09 docs(ffp5cs): bilan découpe god-files (6) + volet String résolu
2026-06-09 refactor(ffp5cs): scinde ota_manager_download.cpp (1362 -> 911)
    downloadFirmwareUltraRevolutionary (fallback micro-chunks) + downloadFilesystem
    (image LittleFS) déplacés vers ota_manager_download_alt.cpp. Méthodes membres
    OTAManager (aucun static/anon-namespace de fichier), bloc d'includes identique.
    Build wroom-test OK. Plus aucun .cpp ffp5cs au-dessus de 1000 lignes.
2026-06-10 [ffp5cs] corrige pertes post reveil ota
2026-06-12 perf(poissonglouton): détection US filtrée sur front, debounce 600 ms, persist NVS lazy, sleep adaptatif nuit/batterie
    - Ultrason : 2 polls consécutifs sous le seuil requis (rejette les échos
    isolés) et déclenchement sur front — l'objet doit sortir du champ avant
    un nouveau comptage, comme l'IR.
    - Debounce global 1500 -> 600 ms : les deux capteurs étant désormais sur
    front, le debounce long ne servait plus qu'à bloquer les bouteilles
    rapprochées (perte ~1/3 à débit soutenu).
2026-06-13 chore(ffp5cs): purge artefacts versionnés et durcit .gitignore
    Retire du suivi git ~418 Mo d'artefacts régénérés ou parasites qui
    n'ont aucun rôle dans le build (framework Arduino via PlatformIO ;
    managed_components/ n'est référencé ni par src/, ni par CMakeLists.txt,
    ni par platformio.ini, ni par la CI).
    - managed_components/ (3404 fichiers, ~398 Mo) : composants ESP-IDF
    récupérés par le component manager, non utilisés par le build Arduino.
2026-06-13 test(ffp5cs): suite native verrouillant le contrat de corps POST HMAC
    Ajoute test/test_post_body/ (Unity, hôte) couvrant Ffp3PostBody::buildFullUpdateBody
    et applyExtraPairs — une des fonctions pures prioritaires de l'audit §3.8, jusqu'ici
    non testée.
    Le corps produit est signé HMAC par le firmware puis reconstruit côté serveur par
    App\Security\Ffp3HmacPostBody::buildFromParams() pour vérifier la signature : l'ordre
    des champs et le format doivent rester strictement identiques des deux côtés, sinon
2026-06-13 test(ffp5cs): complète la couverture du corps POST HMAC (Ffp3PostBody)
    +6 cas sur les trous du contrat firmware<->serveur :
    - capacité des extras (8 max) : overflow ignoré sans débordement
    - bloc suffixe émis après les extras, dans l'ordre serveur fixe
    - parsing applyExtraPairs : segment sans '=', clé vide, segments vides (&&)
    - CARACTÉRISATION d'une divergence potentielle (S1/S2) : un extra à valeur
    vide ('foo=') est ÉMIS, alors que les champs principaux vides sont OMIS.
2026-06-13 test(ffp5cs): stub FreeRTOS natif + couvre la normalisation d'URL OTA
    Débloque le test natif de la logique dépendante de config.h, jusqu'ici
    impossible (config.h -> config_tasks.h -> <freertos/FreeRTOS.h>).
    Infra (test-only, sans impact sur le build firmware qui n'inclut pas test/unit/) :
    - test/unit/freertos/{FreeRTOS,task}.h : stub minimal (UBaseType_t/BaseType_t/
    TickType_t/TaskHandle_t + macros) — juste ce que config_tasks.h exige pour
    ses constexpr de priorité/cœur.
2026-06-14 test(ffp5cs): couvre getServerHostname + getOutputUrl (server_url_config)
    Complète test_server_url : getServerHostname (extraction d'hôte avec parsing
    réel — strip scheme http(s)://, arrêt à ':'/'/' + bornage) et getOutputUrl
    étaient non testés.
    +5 tests : extraction hôte (scheme+port retirés), gardes (null, size 0),
    troncature sans débordement, getOutputUrl bien formé (base + pas de // après
    schéma).
2026-06-14 refactor(ffp5cs): extrait + teste la validation d'epoch (audit 3.8)
    Extrait isValidEpoch (validation NON SIGNÉE anti-overflow : EPOCH_MAX_VALID
    2050 > INT32_MAX, donc comparaison en unsigned obligatoire sur time_t 32-bit)
    et epochAbsDiff de power.cpp vers include/epoch_util.h. Bug-prone et pervasif
    (validation NTP/RTC à 7 endroits) ; un mauvais traitement du dépassement
    INT32_MAX ferait rejeter des horloges valides.
    - include/epoch_util.h : namespace EpochUtil, logique paramétrée (bornes en
2026-06-15 test(ffp5cs): couvre les conversions cm<->mm (seuils d'alerte)
    SensorConfig::Ultrasonic::cmToMm / mmToCmRounded (config_sensors.h) n'étaient
    pas testées alors qu'elles sous-tendent TOUS les seuils d'alerte de niveau
    d'eau (comparaisons mm capteur <-> cm config dans automatism_display.cpp).
    Un bug y fausserait silencieusement tous les déclenchements.
    +3 tests (test pur, aucune modif firmware) :
    - cmToMm (0/1/18/80/1234) ;
2026-06-15 refactor(ffp5cs): C4 étape 2 — extrait ReservoirLowSecurity (debounce+hystérésis réserve basse, pur + tests)
    Deuxième petite extraction de la god-class Automatism, même patron que FloodAlert,
    comportement strictement identique (parité ligne à ligne).
    - Nouveau module pur include/automatism/reservoir_low_security.h
    (ReservoirLowSecurity::evaluate) : debounce (2 verrou / 3 déverrou) + hystérésis
    + zone morte. Aucune dépendance Arduino/config -> testable g++.
    - handleRefillReservoirLowSecurity (automatism_refill.cpp) délègue la décision ;
2026-06-15 refactor(ffp5cs): C4 — interface IActuators (inversion de dépendance god-class) + FakeActuators testé
    Étape structurante du découpage de la god-class Automatism : casse le couplage direct
    Automatism -> SystemActuators concret. Comportement inchangé (dispatch virtuel sur le même objet).
    - Nouvelle interface include/iactuators.h : surface minimale (16 méthodes) consommée par le
    module automatism (vérifiée par grep exhaustif _acts./acts.). Stats pompe non incluses.
    - SystemActuators implémente IActuators (héritage + override). Strictement additif : les autres
    consommateurs (web_server, app_context, realtime_websocket, global acts) gardent le concret.
2026-06-15 refactor(ffp5cs): C4 — extrait RefillStart (décision démarrage remplissage, pur + tests)
    Contrôleur refill : le gating de démarrage de handleRefillAutomaticStart (chemin de SÉCURITÉ)
    est extrait en décision pure testable, désormais possible grâce à IActuators.
    - Nouveau module include/automatism/refill_start.h (RefillStart::evaluate) : Start / BlockReserveLow
    / None selon niveau aquarium/réserve, verrou, essais, mode manuel, pompe active. Aucune dépendance
    Arduino -> testable g++.
    - handleRefillAutomaticStart délègue la décision ; effets de bord (startTankPump, verrou, email,
2026-06-15 refactor(ffp5cs): C4 — interface IMailer (inversion de dépendance messagerie) + FakeMailer testé
    Étape structurante : abstrait Mailer derrière IMailer pour pouvoir tester l'orchestration
    qui envoie des mails (alertes, fin nourrissage, veille/réveil) sans ESP_Mail_Client/réseau.
    Même patron que IActuators. Comportement inchangé (dispatch virtuel sur le même objet).
    - Nouvelle interface include/imailer.h : surface minimale (send, sendAlert, sendSleepMail,
    sendWakeMail) consommée par le module automatism. En-tête léger (SensorReadings en fwd-decl,
    pas de config.h/ESP_Mail_Client ; seul défaut = littéral includeDetailedReport=false).
2026-06-15 refactor(ffp5cs): C4 — extrait FeedingFinalizeOrchestrator (sync fin de nourrissage, testable)
    Avant-dernière orchestration couplée matériel rendue testable nativement.
    Automatism::finalizeFeedingIfNeeded délègue la décision « quoi publier (auto/manuel)
    et quel résultat » à FeedingFinalizeOrchestrator::run, testable via FakeStatusPublisher.
    Approche scopée & peu invasive (1 seule petite interface + params + Outcome) :
    - nouvelle interface MINIMALE include/istatus_publisher.h (publish(SensorReadings&, extraPairs)) ;
    Automatism l'implémente via un mince adaptateur nested forwardant vers sendFullUpdate.
2026-06-16 fix(ffp5cs): concurrence — états partagés multi-tâches en std::atomic (anti-course)
    Convertit trois états mutables partagés, accédés depuis plusieurs tâches FreeRTOS
    sans sérialisation, en std::atomic (style aligné sur net_request_pool.cpp et
    s_heartbeatDroppedCount). Strictement préservateur de comportement, diff minimal.
    - app_tasks.cpp s_bootConfigFetchDone : écrit par netTask (markBootConfigFetchDone),
    lu par loopTask/setup (waitForBootConfigFetch via postConfiguration). volatile -> atomic<bool>.
    - app_tasks.cpp s_wakeProtectionStartMs : écrit par autoTask (markWakeProtectionStart
2026-06-16 docs(ffp5cs): BACKLOG §12 — 3 chantiers // (ClockDecision + atomics + mutex cache distant)
    Documente les 3 PR draft parallèles (fichiers disjoints) : §12.a extraction pure ClockDecision
    (power.cpp, testée + brute-force), §12.b atomics anti-course (s_bootConfigFetchDone /
    s_wakeProtectionStartMs / s_nextSeq), §12.c mutex dédié s_remoteJsonCache (course config distante
    confirmée). Toutes VALIDATION BANC REQUISE.
    https://claude.ai/code/session_01HqRLTTnnpqYD2iWVL9ymso
2026-06-16 test(ffp5cs): couverture native de modules purs non testés
    Ajoute des suites Unity natives pour des modules de logique pure jusque-là
    non couverts (tests uniquement, aucune modification de code de production) :
    - test_board_traits_default / test_board_traits_s3beta : BoardTraits
    (board_traits.h), 13 prédicats constexpr carte/profil/endpoints utilisés
    dans tout le firmware. Les deux suites couvrent respectivement les branches
    « false » (aucune macro définie) et « true » (BOARD_S3/PSRAM/BETA/endpoints),
